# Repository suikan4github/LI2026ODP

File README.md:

# LI2026ODP
Over Drive Processor replacement for the SHARP LI2026A single chip calculator

# Description
The LI2026ODP is an over drive replacement of the SHARP LI2026A "calculator-on-a-chip" LSI.

Without any additional circuit board modification, LI2026ODP allow you to control the all keys and all segments of VFD. You can find a firmware at the [rpn2026 project](https://github.com/suikan4github/rpn2026).

The on board STM32G0B1KET6 micro computer 
has enough speed and memory to run a complex
firmware of a pocket calculator.

In addition to the CAD files, followings are provided in this repository :
- [Schematic diagram](doc/LI2026ODP.pdf). 
- [BOM](doc/LI2026ODP.csv)
- [Design information](doc/design.md)

# Photos

# Requirement
This PCB is designed with :
- KiCAD 5.1.12

# Usage
To use LI2026ODP, simply replace the original LI2026A with the ODP board. Any other modification of the circuit board is not required. 

The SWD and UART port are provided to program and debug the on board microprocessor in the J2 port :

Pin | Description
----|-------------
1   | SWCLK
2   | GND
2   | SWDIO
3   | NRST
4   | LPUART2 TX

# License
This PCB design is distributed by CC0. See [LICENSE](LICENSE) file.

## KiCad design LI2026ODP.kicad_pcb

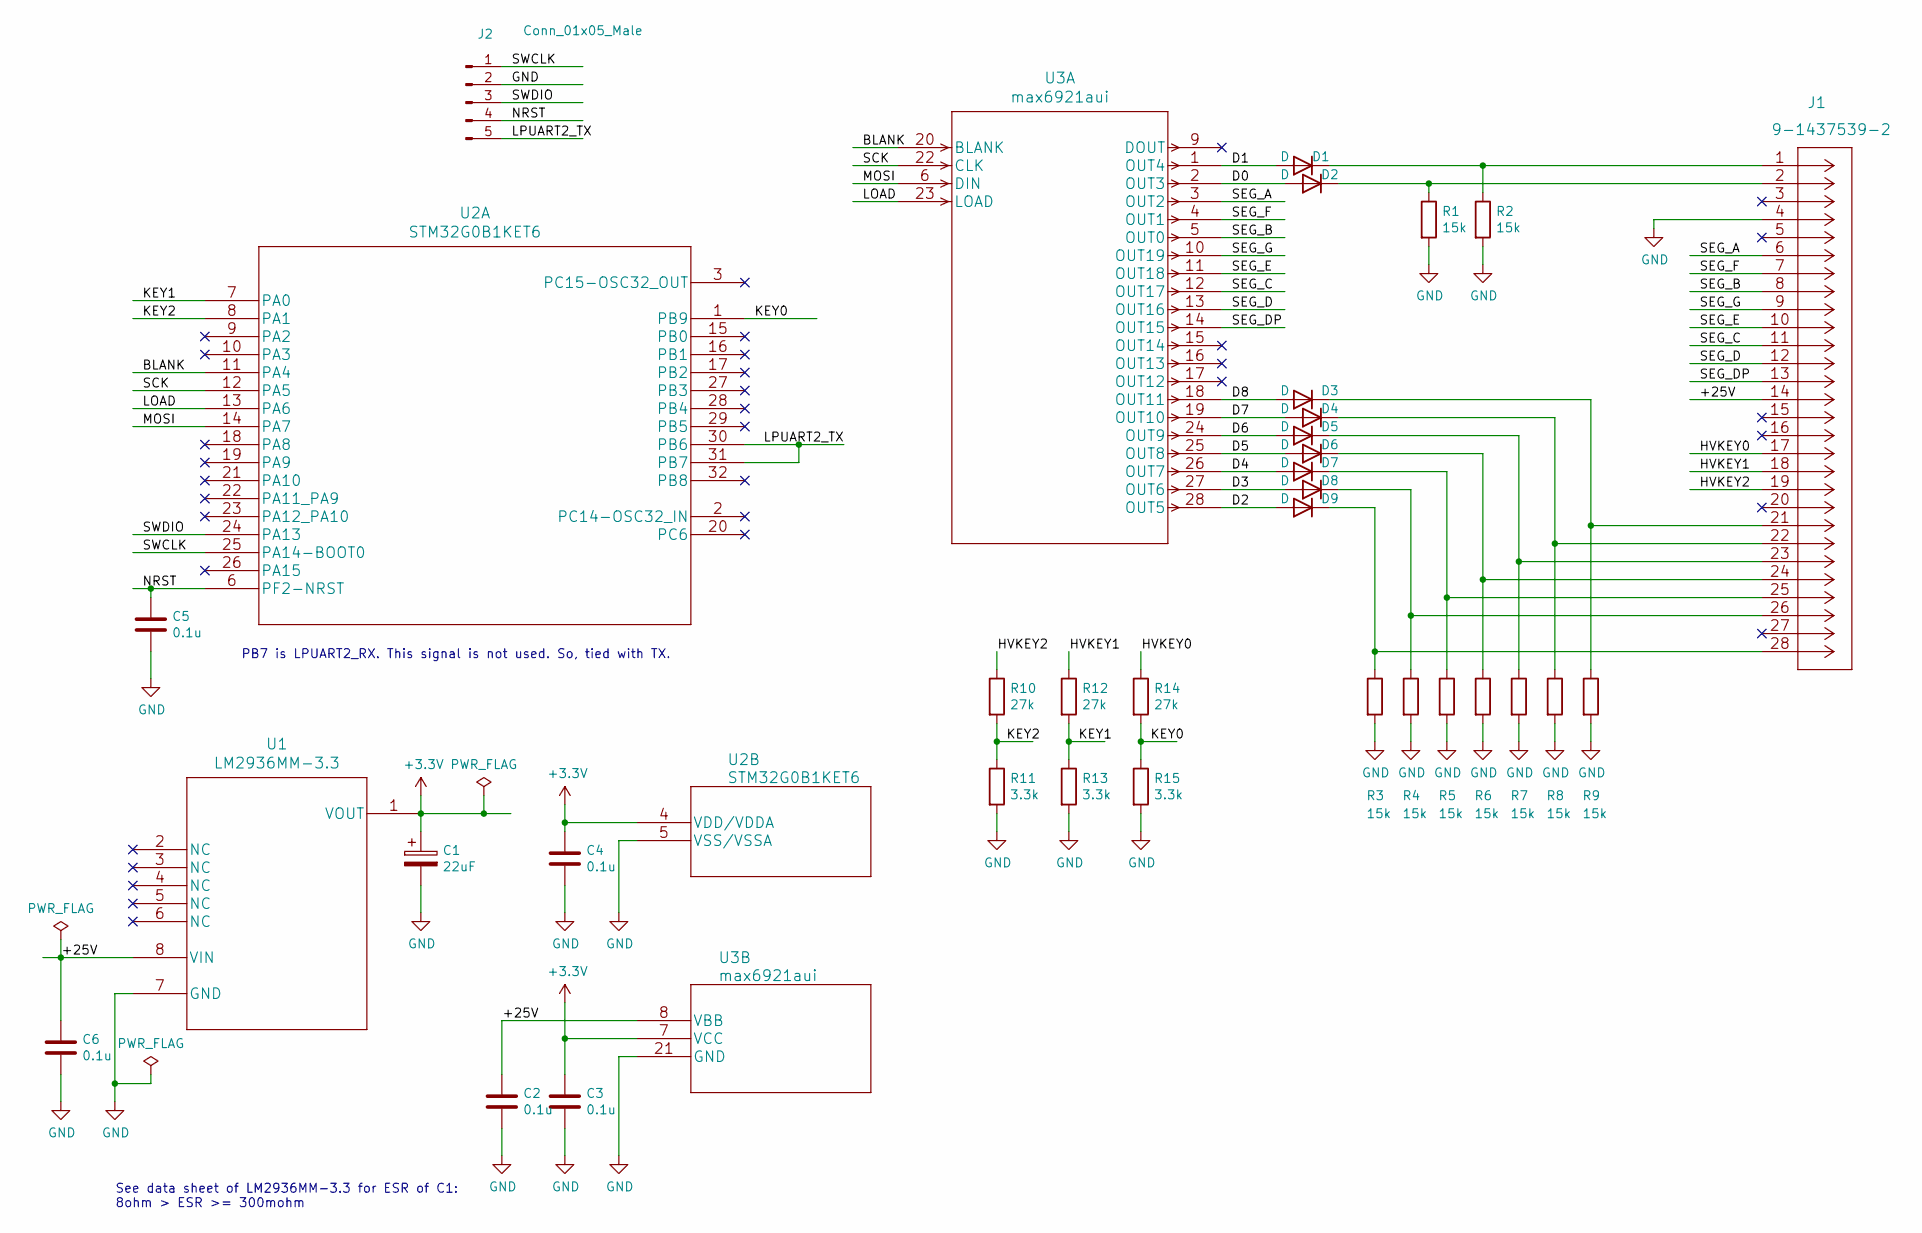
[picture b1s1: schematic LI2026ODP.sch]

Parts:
C1: 22uF; CP_EIA-3216-10_Kemet-I_Pad1.58x1.35mm_HandSolder
C2, C3, C4, C5, C6: 0.1u; C_0603_1608Metric_Pad1.08x0.95mm_HandSolder
D1, D2, D3, D4, D5, D6, D7, D8, D9: D; D_0603_1608Metric_Pad1.05x0.95mm_HandSolder
J1: 9-1437539-2
J2: Conn_01x05_Male; PinHeader_1x05_P2.54mm_Vertical
R1, R2, R3, R4, R5, R6, R7, R8, R9: 15k; R_0603_1608Metric_Pad0.98x0.95mm_HandSolder
R10, R12, R14: 27k; R_0603_1608Metric_Pad0.98x0.95mm_HandSolder
R11, R13, R15: 3.3k; R_0603_1608Metric_Pad0.98x0.95mm_HandSolder
U1: LM2936MM-3.3
U2: STM32G0B1KET6; LQFP-32_7x7mm_P0.8mm
U3: max6921aui

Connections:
+3V3: C1.1, C3.1, C4.1, U1.1 (VOUT), U2.4 (VDD/VDDA), U3.7 (VCC)
/+25V: C2.1, C6.1, J1.14, U1.8 (VIN), U3.8 (VBB)
/BLANK: U2.11 (PA4), U3.20 (BLANK)
/D0: D2.2 (A), U3.2 (OUT3)
/D1: D1.2 (A), U3.1 (OUT4)
/D2: D9.2 (A), U3.28 (OUT5)
/D3: D8.2 (A), U3.27 (OUT6)
/D4: D7.2 (A), U3.26 (OUT7)
/D5: D6.2 (A), U3.25 (OUT8)
/D6: D5.2 (A), U3.24 (OUT9)
/D7: D4.2 (A), U3.19 (OUT10)
/D8: D3.2 (A), U3.18 (OUT11)
/HVKEY0: J1.17, R14.1
/HVKEY1: J1.18, R12.1
/HVKEY2: J1.19, R10.1
/KEY0: R14.2, R15.1, U2.1 (PB9)
/KEY1: R12.2, R13.1, U2.7 (PA0)
/KEY2: R10.2, R11.1, U2.8 (PA1)
/LOAD: U2.13 (PA6), U3.23 (LOAD)
/LPUART2_TX: J2.5, U2.30 (PB6), U2.31 (PB7)
/MOSI: U2.14 (PA7), U3.6 (DIN)
/NRST: C5.1, J2.4, U2.6 (PF2-NRST)
/SCK: U2.12 (PA5), U3.22 (CLK)
/SEG_A: J1.6, U3.3 (OUT2)
/SEG_B: J1.8, U3.5 (OUT0)
/SEG_C: J1.11, U3.12 (OUT17)
/SEG_D: J1.12, U3.13 (OUT16)
/SEG_DP: J1.13, U3.14 (OUT15)
/SEG_E: J1.10, U3.11 (OUT18)
/SEG_F: J1.7, U3.4 (OUT1)
/SEG_G: J1.9, U3.10 (OUT19)
/SWCLK: J2.1, U2.25 (PA14-BOOT0)
/SWDIO: J2.3, U2.24 (PA13)
GND: C1.2, C2.2, C3.2, C4.2, C5.2, C6.2, J1.4, J2.2, R1.2, R2.2, R3.2, R4.2, R5.2, R6.2, R7.2, R8.2, R9.2, R11.2, R13.2, R15.2, U1.7 (GND), U2.5 (VSS/VSSA), U3.21 (GND)
unnamed: D1.1 (K), J1.1, R2.1
unnamed: D2.1 (K), J1.2, R1.1
unnamed: D3.1 (K), J1.21, R9.1
unnamed: D4.1 (K), J1.22, R8.1
unnamed: D5.1 (K), J1.23, R7.1
unnamed: D6.1 (K), J1.24, R6.1
unnamed: D7.1 (K), J1.25, R5.1
unnamed: D8.1 (K), J1.26, R4.1
unnamed: D9.1 (K), J1.28, R3.1

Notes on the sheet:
PB7 is LPUART2_RX. This signal is not used. So, tied with TX.
See data sheet of LM2936MM-3.3 for ESR of C1: 8ohm > ESR >= 300mohm

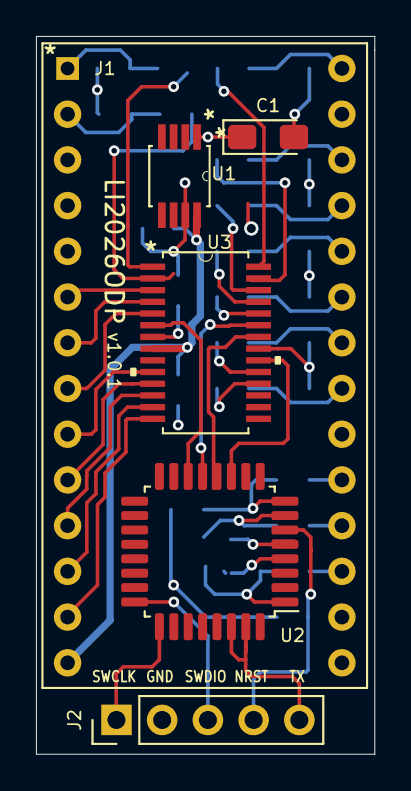
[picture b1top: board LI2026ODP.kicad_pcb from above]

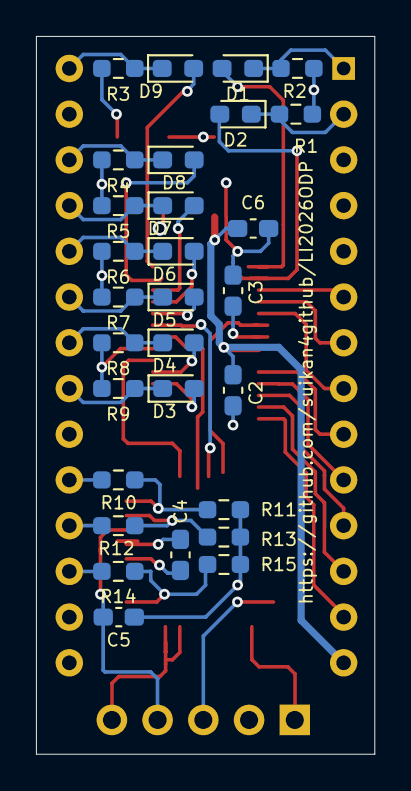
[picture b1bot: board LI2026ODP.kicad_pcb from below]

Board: 4 copper layers, 18.8 x 39.9 mm, 35 parts (29 on the bottom side), 43 nets.

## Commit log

2022-01-07 Starting layout.
2022-01-08 All parts connected.
    Waiting for the routing.
2022-01-08 Change SMD from 1005M to 1608M
2022-01-08 layout finished.
2022-01-08 Fix the BLANK bug and change layout
    - BLANK was incorrectly tied with 3.3v
    - Make layer 3 as +3.3v
    - Make 25v line as 0.4mm
    - Change RKEY1,2,3 pins for the simple layout.
2022-01-09 Change voltage regulator
    from 3.0 to 3.3v
2022-01-09 Clean up the wire in the power layer.
2022-01-09 Schematics and Layouts refreshed.
    Unsed comments are deleted.
2022-01-09 The bypass capacitor layout of the microprocessor is optimized.
2022-01-09 Update C1 from 1608 to 2012
2022-01-09 Move LSI's to left
    To align them ceter of the board.
2022-01-09 Add capacitor to NRST for noise protection.
2022-01-09 Add BOM file
2022-01-09 Change BLANK control of MAX6921
    from the hardwired to the software control.
2022-01-09 Add CHANGELOG.
2022-01-09 Create LICENSE
2022-01-09 Add README comment
    Also add PDF schematics.
2022-01-10 Add gerber file output
2022-01-10 Rename the key matrix signals.
    Aligned with the program ( zero origine ).
2022-01-10 Place order to Fusion PCB
2022-01-11 Document update
2022-01-11 update design.md
    explicitly declare "N.A." in the pin assignment of VFD driver.
2022-01-11 Add link to the LSIs
2022-01-11 Add link to the devices.
    Also, add section information of the datasheet and the reference manual.
2022-01-16 Refine the DESIGN.md
    To make the English better.
2022-01-29 Add design note.
    Issue #3
2022-01-29 Refined bypass capacitor allocation.
    Issue #7
    Swapped C3 and C4 on the schematics. PCB layout is kept.
    This is for ease of read the schematic/layout.
2022-01-29 Added SWCLK silk to PCB.
    Add SWCLK silk
    Issue : #6
    This was missing in the original design.
2022-01-30 Modify the U2 Footprint.
    Issue : #5
    The footprint was incorrect. Substitute it with the right 0.8mm pitch one.
2022-01-30 Add capacitor for 25v line
    Issue #8 .
    Add C6 close to the voltage regulator.
2022-01-30 Version number should be updated.
    Issue : #9
    Update silk of PCB from 1.0.0 to 1.0.1
2022-01-31 Update schematics and BOM table.
    Add C6. Also, update the sheet data
    (date, version...)

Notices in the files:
parts and their libraries:
Copyright 2021 Accelerated Designs. All rights reserved.
